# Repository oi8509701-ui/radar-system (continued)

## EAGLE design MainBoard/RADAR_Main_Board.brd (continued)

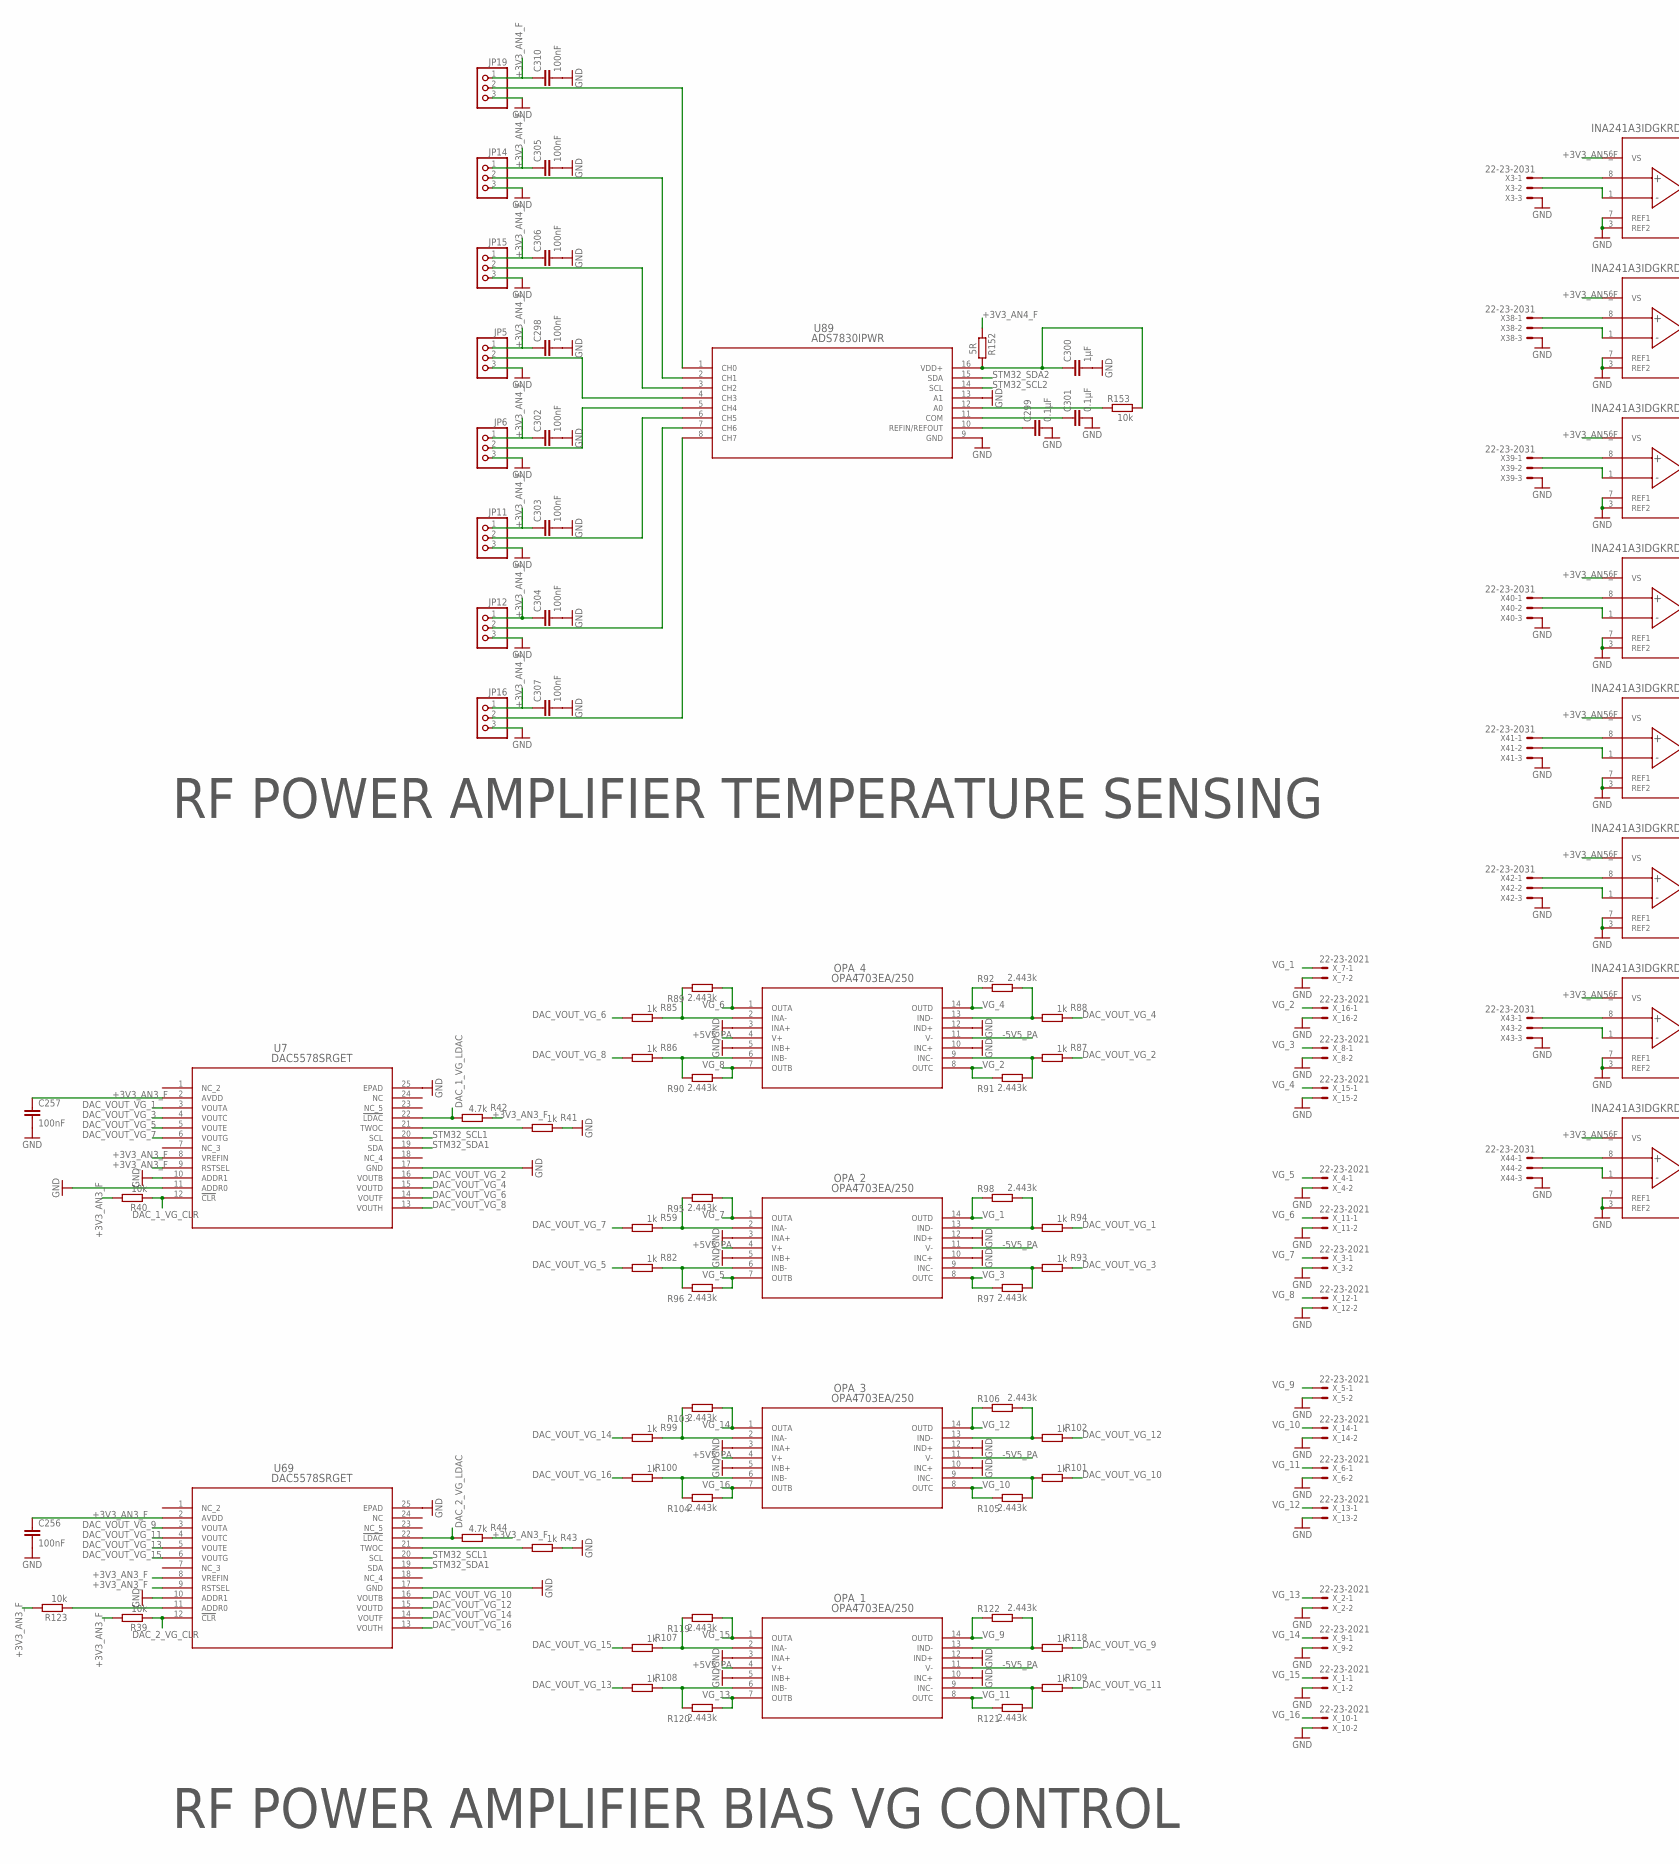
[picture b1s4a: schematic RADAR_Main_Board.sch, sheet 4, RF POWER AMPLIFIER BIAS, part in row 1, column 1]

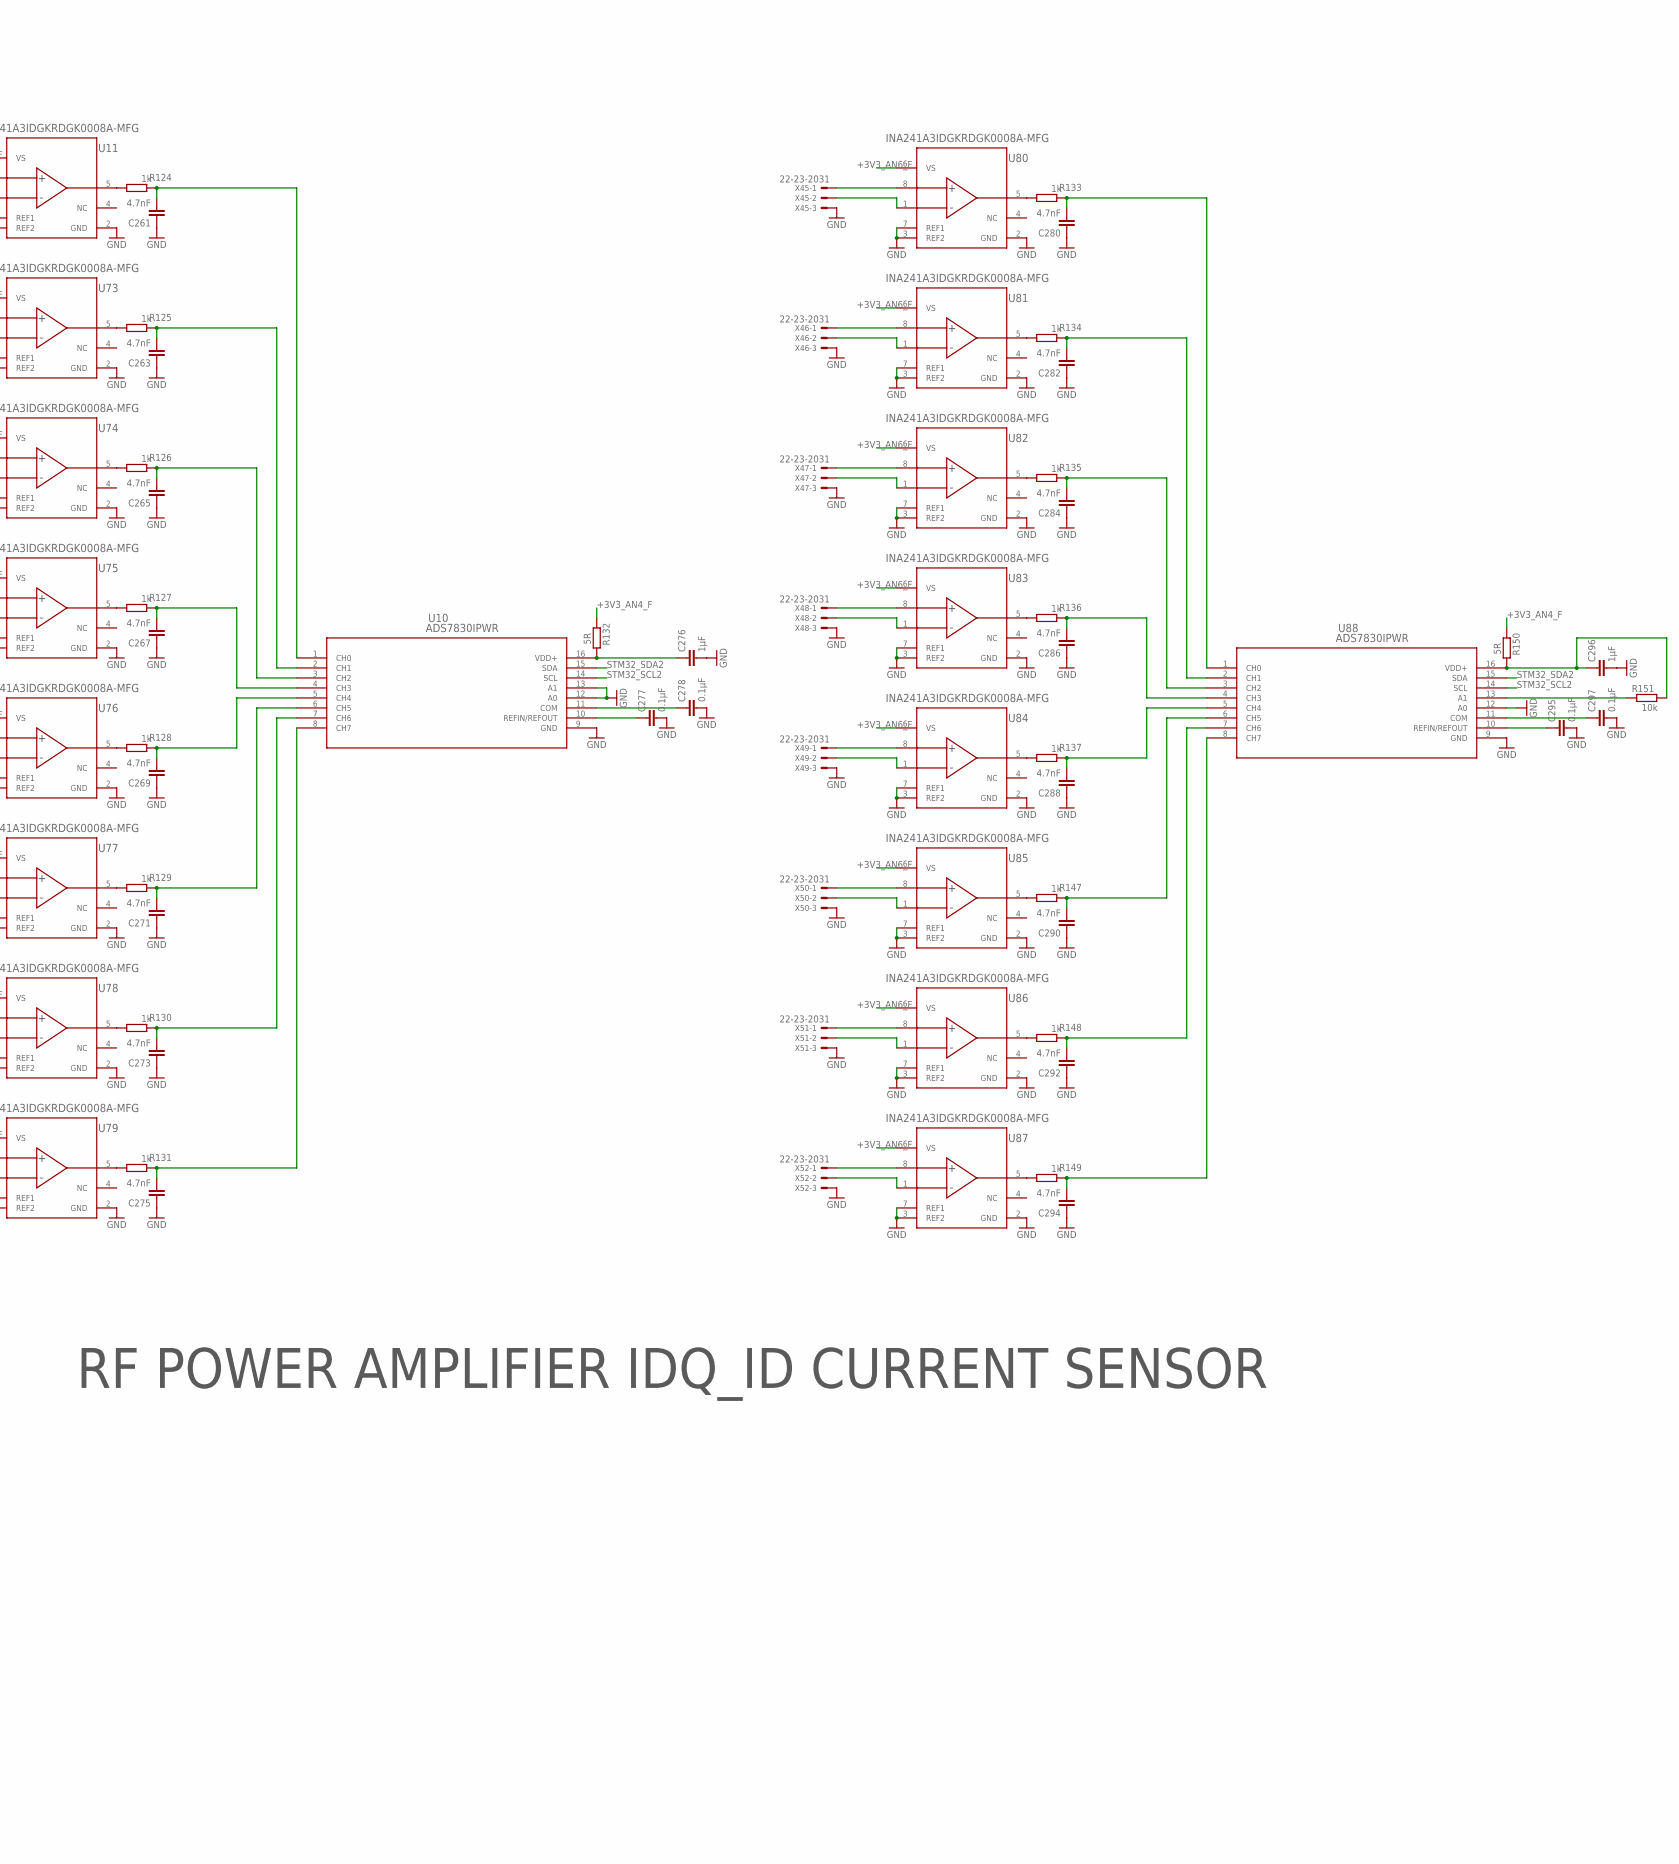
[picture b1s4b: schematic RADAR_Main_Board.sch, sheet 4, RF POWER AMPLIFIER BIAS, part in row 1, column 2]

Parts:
C256, C257, C298, C302, C303, C304, C305, C306, C307, C310: 100nF; C0201
C261, C263, C265, C267, C269, C271, C273, C275, C280, C282, C284, C286, C288, C290, C292, C294: 4.7nF; C0201
C276, C296, C300: 1µF; C0201
C277, C278, C295, C297, C299, C301: 0.1µF; C0201
JP5, JP6, JP11, JP12, JP14, JP15, JP16, JP19: PINHD-1X3; 1X03
OPA_1, OPA_2, OPA_3, OPA_4: OPA4703EA/250; PW14
R39, R40, R123, R151, R153: 10k; R0201
R41, R43, R59, R82, R85, R86, R87, R88, R93, R94, R99, R100, R101, R102, R107, R108, R109, R118, R124, R125, R126, R127, R128, R129, R130, R131, R133, R134, R135, R136, R137, R147, R148, R149: 1k; R0201
R42, R44: 4.7k; R0201
R89, R90, R91, R92, R95, R96, R97, R98, R103, R104, R105, R106, R119, R120, R121, R122: 2.443k; R0201
R132, R150, R152: 5R; R0201
U7, U69: DAC5578SRGET; RGE24_2P7X2P7
U10, U88, U89: ADS7830IPWR; PW16
U11, U73, U74, U75, U76, U77, U78, U79, U80, U81, U82, U83, U84, U85, U86, U87: INA241A3IDGKRDGK0008A-MFG; DGK0008A-MFG
X3, X38, X39, X40, X41, X42, X43, X44, X45, X46, X47, X48, X49, X50, X51, X52: 22-23-2031
X_1, X_2, X_3, X_4, X_5, X_6, X_7, X_8, X_9, X_10, X_11, X_12, X_13, X_14, X_15, X_16: 22-23-2021

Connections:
+3V3_AN3_F: C256.1, C257.1, R39.2, R40.2, R42.1, R44.1, R123.2, U7.2 (AVDD), U7.8 (VREFIN), U7.9 (RSTSEL), U69.2 (AVDD), U69.8 (VREFIN), U69.9 (RSTSEL); also elsewhere on the board
+3V3_AN4_F: C298.1, C302.1, C303.1, C304.1, C305.1, C306.1, C307.1, C310.1, JP5.1, JP6.1, JP11.1, JP12.1, JP14.1, JP15.1, JP16.1, JP19.1, R132.1, R150.1, R152.1; also elsewhere on the board
+3V3_AN5_F: U11.6 (VS), U73.6 (VS), U74.6 (VS), U75.6 (VS), U76.6 (VS), U77.6 (VS), U78.6 (VS), U79.6 (VS); also elsewhere on the board
+3V3_AN6_F: U80.6 (VS), U81.6 (VS), U82.6 (VS), U83.6 (VS), U84.6 (VS), U85.6 (VS), U86.6 (VS), U87.6 (VS); also elsewhere on the board
+5V5_PA: OPA_1.4 (V+), OPA_2.4 (V+), OPA_3.4 (V+), OPA_4.4 (V+); also elsewhere on the board
-5V5_PA: OPA_1.11 (V-), OPA_2.11 (V-), OPA_3.11 (V-), OPA_4.11 (V-); also elsewhere on the board
DAC_1_VG_CLR: R40.1, U7.12 (!CLR); also elsewhere on the board
DAC_1_VG_LDAC: R42.2, U7.22 (!LDAC); also elsewhere on the board
DAC_2_VG_CLR: R39.1, U69.12 (!CLR); also elsewhere on the board
DAC_2_VG_LDAC: R44.2, U69.22 (!LDAC); also elsewhere on the board
DAC_VOUT_VG_1: R94.1, U7.3 (VOUTA)
DAC_VOUT_VG_2: R87.1, U7.16 (VOUTB)
DAC_VOUT_VG_3: R93.1, U7.4 (VOUTC)
DAC_VOUT_VG_4: R88.1, U7.15 (VOUTD)
DAC_VOUT_VG_5: R82.2, U7.5 (VOUTE)
DAC_VOUT_VG_6: R85.2, U7.14 (VOUTF)
DAC_VOUT_VG_7: R59.2, U7.6 (VOUTG)
DAC_VOUT_VG_8: R86.2, U7.13 (VOUTH)
DAC_VOUT_VG_9: R118.1, U69.3 (VOUTA)
DAC_VOUT_VG_10: R101.1, U69.16 (VOUTB)
DAC_VOUT_VG_11: R109.1, U69.4 (VOUTC)
DAC_VOUT_VG_12: R102.1, U69.15 (VOUTD)
DAC_VOUT_VG_13: R108.2, U69.5 (VOUTE)
DAC_VOUT_VG_14: R99.2, U69.14 (VOUTF)
DAC_VOUT_VG_15: R107.2, U69.6 (VOUTG)
DAC_VOUT_VG_16: R100.2, U69.13 (VOUTH)
GND: C256.2, C257.2, C261.1, C263.1, C265.1, C267.1, C269.1, C271.1, C273.1, C275.1, C276.2, C277.2, C278.2, C280.1, C282.1, C284.1, C286.1, C288.1, C290.1, C292.1, C294.1, C295.2, C296.2, C297.2, C298.2, C299.2, C300.2, C301.2, C302.2, C303.2, C304.2, C305.2, C306.2, C307.2, C310.2, JP5.3, JP6.3, JP11.3, JP12.3, JP14.3, JP15.3, JP16.3, JP19.3, OPA_1.3 (INA+), OPA_1.5 (INB+), OPA_1.10 (INC+), OPA_1.12 (IND+), OPA_2.3 (INA+), OPA_2.5 (INB+), OPA_2.10 (INC+), OPA_2.12 (IND+), OPA_3.3 (INA+), OPA_3.5 (INB+), OPA_3.10 (INC+), OPA_3.12 (IND+), OPA_4.3 (INA+), OPA_4.5 (INB+), OPA_4.10 (INC+), OPA_4.12 (IND+), R41.1, R43.1, U7.10 (ADDR1), U7.11 (ADDR0), U7.17 (GND), U7.25 (EPAD), U10.9 (GND), U10.12 (A0), U10.13 (A1), U11.2 (GND), U11.3 (REF2), U11.7 (REF1), U69.10 (ADDR1), U69.17 (GND), U69.25 (EPAD), U73.2 (GND), U73.3 (REF2), U73.7 (REF1), U74.2 (GND), U74.3 (REF2), U74.7 (REF1), U75.2 (GND), U75.3 (REF2), U75.7 (REF1), U76.2 (GND), U76.3 (REF2), U76.7 (REF1), U77.2 (GND), U77.3 (REF2), U77.7 (REF1), U78.2 (GND), U78.3 (REF2), U78.7 (REF1), U79.2 (GND), U79.3 (REF2), U79.7 (REF1), U80.2 (GND), U80.3 (REF2), U80.7 (REF1), U81.2 (GND), U81.3 (REF2), U81.7 (REF1), U82.2 (GND), U82.3 (REF2), U82.7 (REF1), U83.2 (GND), U83.3 (REF2), U83.7 (REF1), U84.2 (GND), U84.3 (REF2), U84.7 (REF1), U85.2 (GND), U85.3 (REF2), U85.7 (REF1), U86.2 (GND), U86.3 (REF2), U86.7 (REF1), U87.2 (GND), U87.3 (REF2), U87.7 (REF1), U88.9 (GND), U88.12 (A0), U89.9 (GND), U89.13 (A1), X3.3, X38.3, X39.3, X40.3, X41.3, X42.3, X43.3, X44.3, X45.3, X46.3, X47.3, X48.3, X49.3, X50.3, X51.3, X52.3, X_1.2, X_2.2, X_3.2, X_4.2, X_5.2, X_6.2, X_7.2, X_8.2, X_9.2, X_10.2, X_11.2, X_12.2, X_13.2, X_14.2, X_15.2, X_16.2; also elsewhere on the board
unnamed: R123.1, U69.11 (ADDR0)
unnamed: R43.2, U69.21 (TWOC)
unnamed: OPA_4.2 (INA-), R85.1, R89.1
unnamed: U11.8 (IN+), X3.1
unnamed: OPA_4.6 (INB-), R86.1, R90.1
unnamed: U11.1 (IN-), X3.2
unnamed: R124.2, U11.5 (OUT)
unnamed: C261.2, R124.1, U10.1 (CH0)
unnamed: U73.8 (IN+), X38.1
unnamed: OPA_4.9 (INC-), R87.2, R91.2
unnamed: U73.1 (IN-), X38.2
unnamed: R125.2, U73.5 (OUT)
unnamed: OPA_4.13 (IND-), R88.2, R92.2
unnamed: C263.2, R125.1, U10.2 (CH1)
unnamed: U74.8 (IN+), X39.1
unnamed: U74.1 (IN-), X39.2
unnamed: R126.2, U74.5 (OUT)
unnamed: R41.2, U7.21 (TWOC)
unnamed: OPA_2.2 (INA-), R59.1, R95.1
unnamed: C265.2, R126.1, U10.3 (CH2)
unnamed: OPA_2.6 (INB-), R82.1, R96.1
unnamed: U75.8 (IN+), X40.1
unnamed: U75.1 (IN-), X40.2
unnamed: R127.2, U75.5 (OUT)
unnamed: OPA_2.9 (INC-), R93.2, R97.2
unnamed: C267.2, R127.1, U10.4 (CH3)
unnamed: U76.8 (IN+), X41.1
unnamed: OPA_2.13 (IND-), R94.2, R98.2
unnamed: U76.1 (IN-), X41.2
unnamed: R128.2, U76.5 (OUT)
unnamed: C269.2, R128.1, U10.5 (CH4)
unnamed: U77.8 (IN+), X42.1
unnamed: U77.1 (IN-), X42.2
unnamed: R129.2, U77.5 (OUT)
unnamed: OPA_3.2 (INA-), R99.1, R103.1
unnamed: C271.2, R129.1, U10.6 (CH5)
unnamed: OPA_3.6 (INB-), R100.1, R104.1
unnamed: U78.8 (IN+), X43.1
unnamed: U78.1 (IN-), X43.2
unnamed: R130.2, U78.5 (OUT)
unnamed: OPA_3.9 (INC-), R101.2, R105.2
unnamed: C273.2, R130.1, U10.7 (CH6)
unnamed: U79.8 (IN+), X44.1
unnamed: OPA_3.13 (IND-), R102.2, R106.2
unnamed: U79.1 (IN-), X44.2
unnamed: R131.2, U79.5 (OUT)
unnamed: C275.2, R131.1, U10.8 (CH7)
unnamed: C277.1, U10.10 (REFIN/REFOUT)
unnamed: C276.1, R132.2, U10.16 (VDD+)
unnamed: C278.1, U10.11 (COM)
unnamed: OPA_1.2 (INA-), R107.1, R119.1
unnamed: U80.8 (IN+), X45.1
unnamed: OPA_1.6 (INB-), R108.1, R120.1
unnamed: U80.1 (IN-), X45.2
unnamed: R133.2, U80.5 (OUT)
unnamed: C280.2, R133.1, U88.1 (CH0)
unnamed: OPA_1.9 (INC-), R109.2, R121.2
unnamed: U81.8 (IN+), X46.1
unnamed: U81.1 (IN-), X46.2
unnamed: OPA_1.13 (IND-), R118.2, R122.2
unnamed: R134.2, U81.5 (OUT)
unnamed: C282.2, R134.1, U88.2 (CH1)
unnamed: U82.8 (IN+), X47.1
unnamed: U82.1 (IN-), X47.2
unnamed: R135.2, U82.5 (OUT)
unnamed: C284.2, R135.1, U88.3 (CH2)
unnamed: U83.8 (IN+), X48.1
unnamed: U83.1 (IN-), X48.2
unnamed: R136.2, U83.5 (OUT)
unnamed: C286.2, R136.1, U88.4 (CH3)
unnamed: U84.8 (IN+), X49.1
unnamed: U84.1 (IN-), X49.2
unnamed: R137.2, U84.5 (OUT)
unnamed: C288.2, R137.1, U88.5 (CH4)
unnamed: U85.8 (IN+), X50.1
unnamed: U85.1 (IN-), X50.2
unnamed: R147.2, U85.5 (OUT)
unnamed: C290.2, R147.1, U88.6 (CH5)
unnamed: U86.8 (IN+), X51.1
unnamed: U86.1 (IN-), X51.2
unnamed: R148.2, U86.5 (OUT)
unnamed: C292.2, R148.1, U88.7 (CH6)
unnamed: U87.8 (IN+), X52.1
unnamed: U87.1 (IN-), X52.2
unnamed: R149.2, U87.5 (OUT)
unnamed: C294.2, R149.1, U88.8 (CH7)
unnamed: C295.1, U88.10 (REFIN/REFOUT)
unnamed: C296.1, R150.2, R151.2, U88.16 (VDD+)
unnamed: C297.1, U88.11 (COM)
unnamed: R151.1, U88.13 (A1)
unnamed: R153.1, U89.12 (A0)
unnamed: JP5.2, U89.4 (CH3)
unnamed: JP6.2, U89.5 (CH4)
unnamed: JP19.2, U89.1 (CH0)
unnamed: JP12.2, U89.7 (CH6)
unnamed: JP14.2, U89.2 (CH1)
unnamed: JP16.2, U89.8 (CH7)
unnamed: C299.1, U89.10 (REFIN/REFOUT)
unnamed: C300.1, R152.2, R153.2, U89.16 (VDD+)
unnamed: C301.1, U89.11 (COM)
unnamed: JP11.2, U89.6 (CH5)
unnamed: JP15.2, U89.3 (CH2)
STM32_SCL1: U7.20 (SCL), U69.20 (SCL); also elsewhere on the board
STM32_SCL2: U10.14 (SCL), U88.14 (SCL), U89.14 (SCL); also elsewhere on the board
STM32_SDA1: U7.19 (SDA), U69.19 (SDA); also elsewhere on the board
STM32_SDA2: U10.15 (SDA), U88.15 (SDA), U89.15 (SDA); also elsewhere on the board
VG_1: OPA_2.14 (OUTD), R98.1, X_7.1
VG_2: OPA_4.8 (OUTC), R91.1, X_16.1
VG_3: OPA_2.8 (OUTC), R97.1, X_8.1
VG_4: OPA_4.14 (OUTD), R92.1, X_15.1
VG_5: OPA_2.7 (OUTB), R96.2, X_4.1
VG_6: OPA_4.1 (OUTA), R89.2, X_11.1
VG_7: OPA_2.1 (OUTA), R95.2, X_3.1
VG_8: OPA_4.7 (OUTB), R90.2, X_12.1
VG_9: OPA_1.14 (OUTD), R122.1, X_5.1
VG_10: OPA_3.8 (OUTC), R105.1, X_14.1
VG_11: OPA_1.8 (OUTC), R121.1, X_6.1
VG_12: OPA_3.14 (OUTD), R106.1, X_13.1
VG_13: OPA_1.7 (OUTB), R120.2, X_2.1
VG_14: OPA_3.1 (OUTA), R103.2, X_9.1
VG_15: OPA_1.1 (OUTA), R119.2, X_1.1
VG_16: OPA_3.7 (OUTB), R104.2, X_10.1

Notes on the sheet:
RF POWER AMPLIFIER IDQ_ID CURRENT SENSOR
RF POWER AMPLIFIER BIAS VG CONTROL
RF POWER AMPLIFIER TEMPERATURE SENSING

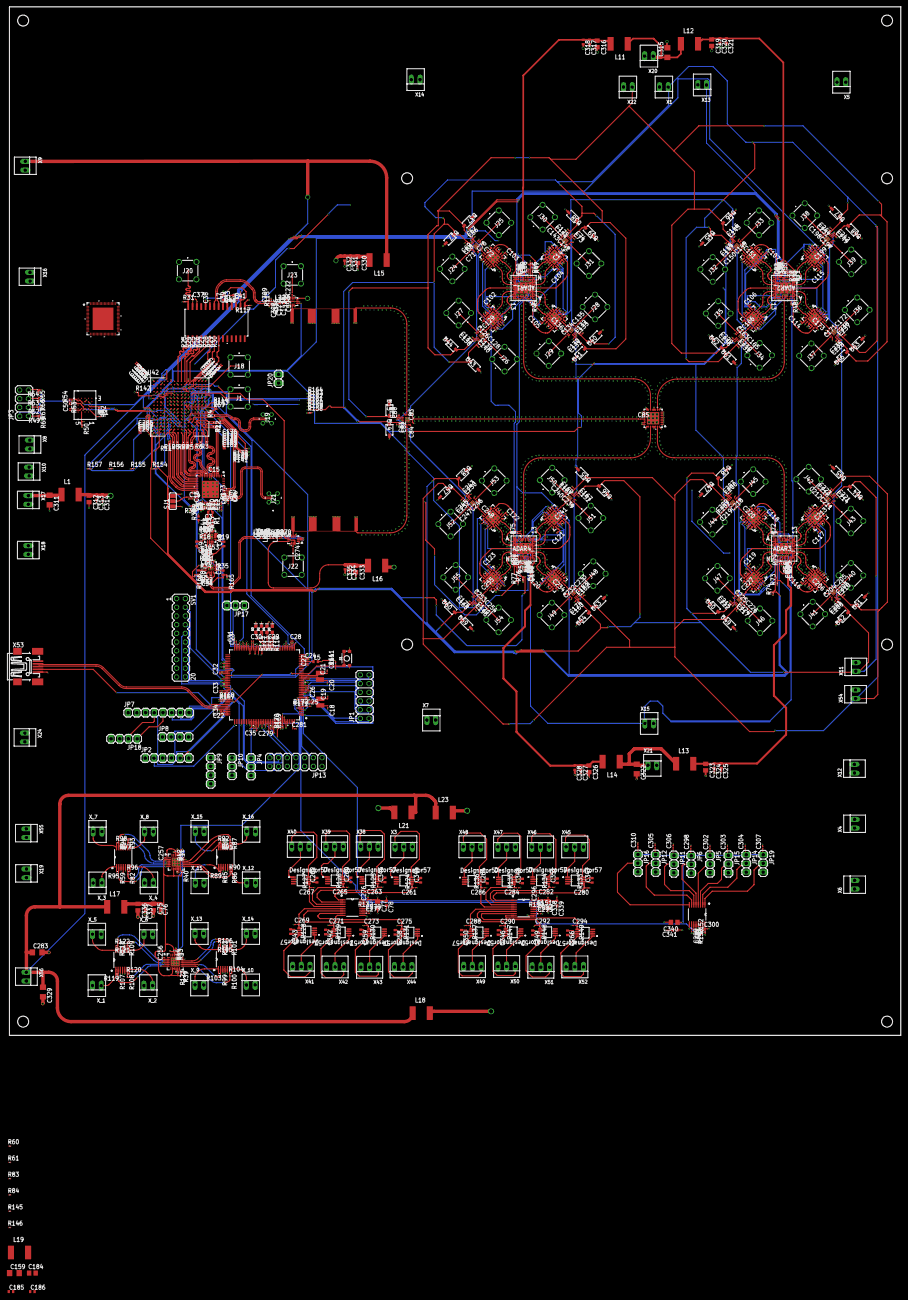
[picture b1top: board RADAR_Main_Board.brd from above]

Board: 10 copper layers, 260.0 x 300.0 mm, 776 parts (0 on the bottom side), 622 nets.

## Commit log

2026-03-31 Initial commit: Fractal 32x16 antenna array with simulation reports and images
2026-03-31 Add README.md with simulation results and specifications
2026-03-31 Add HTML documentation page
2026-03-31 Update README.md (plain text)
2026-03-31 Add PowerBoard: PCB, BOM, and power diagram
2026-03-31 Add PowerBoard README_EN.md (English documentation)
2026-03-31 Create LICENSE
2026-04-01 Add complete system architecture diagram (v2.0)
    - Full schematic with all components from RADAR_V6_V2.png
    - 16 Antenna Tiles (32×16 = 512 elements each, total 8,192)
    - External Interfaces: 10G Ethernet (PRIMARY), USB 3.0 (BACKUP), GPIO, Ext Ref, JTAG
    - Clock System: OCXO (ECOC-2522), XO (CCHD-957), VCXO (CVHD-950), AD9523
    - LO System: 2× ADF4382, Balun (MTX2-143+), Attenuator PAD (ATS1005-3DB)
    - RF Chain: 2× RF Switch (M3SWA2-34DR+), Combiner (EP4RKU+)
2026-04-01 Add system architecture diagram (PDF)
2026-04-01 Replace AERIS_10N_System_Architecture.pdf (Version 2.0 FIXED)
    FIXED: Architecture Blocks table formatting
    Changes:
    - Split single large table into 10 smaller tables
    - Removed HTML tags from cells
    - Improved text formatting and readability
    - Better page breaks (3 pages total)
2026-04-01 Add complete Wiki documentation (12 pages)
    New pages:
    1. Home.md - Main page with project overview and navigation
    2. System-Architecture.md - Complete system architecture documentation
    3. Hardware-Specifications.md - Full BOM and component details
    4. RF-Chain-Documentation.md - TX/RX signal paths and gain budgets
    5. Antenna-Array.md - 16-tile architecture and beamforming
2026-04-01 Add Simulations directory for fractal H-tree array
    New structure for fractal H-tree phased array simulations:
    Simulations/
    ├── README.md # Main documentation
    ├── Array_Pattern/ # Array pattern simulations
    │ ├── antenna_array_fractal.m # NEW: Fractal H-tree 4×4 array
    │ ├── Antenna_array.m # Original (reference)
2026-04-01 Update QWEN.md with honest range table by target type
    Added realistic detection range table based on target RCS:
    Configurations:
    - AERIS-10N (Nexus): 1 tile, 16 elements, 4 channels, ~18 dBi, ~1W
    - AERIS-10E/X (Extended): 16 tiles, 256 elements, 64 channels, ~30 dBi, ~160W
    Detection Range by Target:
    - Elephant (100 m²): 3 km (Nexus), 20 km (Extended)
2026-04-01 Add MCP Server documentation and push to GitHub
    Added comprehensive MCP Server documentation:
    1. QWEN.md:
    - Added new section 'MCP Server (KiCad Integration)'
    - Documented all 5 available tools
    - Added usage examples with JSON requests/responses
    - Added integration examples with AI assistants
2026-04-01 AUTOMATED: Add missing connectors to MainBoard
    🤖 FULLY AUTOMATED - NO MANUAL WORK
    Added via auto_add_connectors.py:
    ✅ J_PWR_IN (20-pin) - Power input from Power Board
    ✅ J_TILE_SYNC (50-pin) - Tile Sync Controller interface
    ✅ J_PA_BIAS (20-pin) - PA Board bias control
    Generated files:
2026-04-01 🤖 AUTOMATED: MainBoard connector addition complete
    Fully automated workflow completed:
    ✅ Connectors added (J_PWR_IN, J_TILE_SYNC, J_PA_BIAS)
    ✅ Nets connected automatically
    ✅ PCB updated from schematic
    ✅ DRC passed
    ✅ Gerbers exported
2026-04-01 Revert "🤖 AUTOMATED: MainBoard connector addition complete"
    This reverts commit 02bcae12662c453d425235cc63a022ba9474ca3a.
2026-04-01 🔧 FIXED: All components within board boundaries
    Reverted previous commit with errors.
    Fixed 225/784 components that were outside board edges.
    Changes:
    - All components moved inside 280×200mm board
    - 5mm margin from all edges enforced
    - Connectors placed properly:
2026-04-01 ❌ REMOVE MainBoard from repository - needs complete redesign
2026-04-01 📚 Added KiCad Usage Rules to QWEN.md
    Added comprehensive KiCad usage guide:
    ⚠️ DOs and DON'Ts:
    - ❌ NO text editing of .kicad_pcb files
    - ❌ NO regex replacements
    - ✅ USE KiCad PCB Editor
    - ✅ USE KiCad Python API via Tools → Scripting
2026-04-01 ❌ REMOVE MainBoard/RADAR_Main_Board directory from repository
    Removed working PCB files from version control:
    - RADAR_Main_Board.kicad_pcb
    - RADAR_Main_Board.kicad_sch
    - RADAR_Main_Board.pretty/ (footprints)
    - All backup files
    Reason: Large binary files, frequent changes during development.
2026-04-01 📚 Added complete KiCAD-MCP-Server documentation to QWEN.md
    Added comprehensive guide (400+ lines):
    - Installation instructions (macOS)
    - Server startup guide
    - 122 tools overview (6 categories)
    - Python API examples (4 examples)
    - AERIS-10N scripts documentation
2026-04-03 ✅ Add ready boards: BACKPLANE_16T, PowerAmplifier, FreqSynthesizer
    - BACKPLANE_16T_v1.kicad_pcb: Motherboard for 16 tiles sync
    - PowerAmplifierBoard/RF_PA.kicad_pcb: 10W GaN PA board
    - FreqSynthesizer MCP_ROUTED: Clock distribution board
    - READY_BOARDS.md: Documentation for ready boards
    Status: Ready for production
    Date: 2026-04-02
2026-04-05 remove all files, keep wiki only
2026-04-05 add: TR_Module_10GHz PCB + BOM
2026-04-06 update: autorouted PCB (22/36 nets, 1789 segments)
2026-04-06 Revert "update: autorouted PCB (22/36 nets, 1789 segments)"
    This reverts commit aaf4b5bc0dab927e93ae8dcb000f6a615e5b2f24.
2026-04-13 Remove wiki folder
